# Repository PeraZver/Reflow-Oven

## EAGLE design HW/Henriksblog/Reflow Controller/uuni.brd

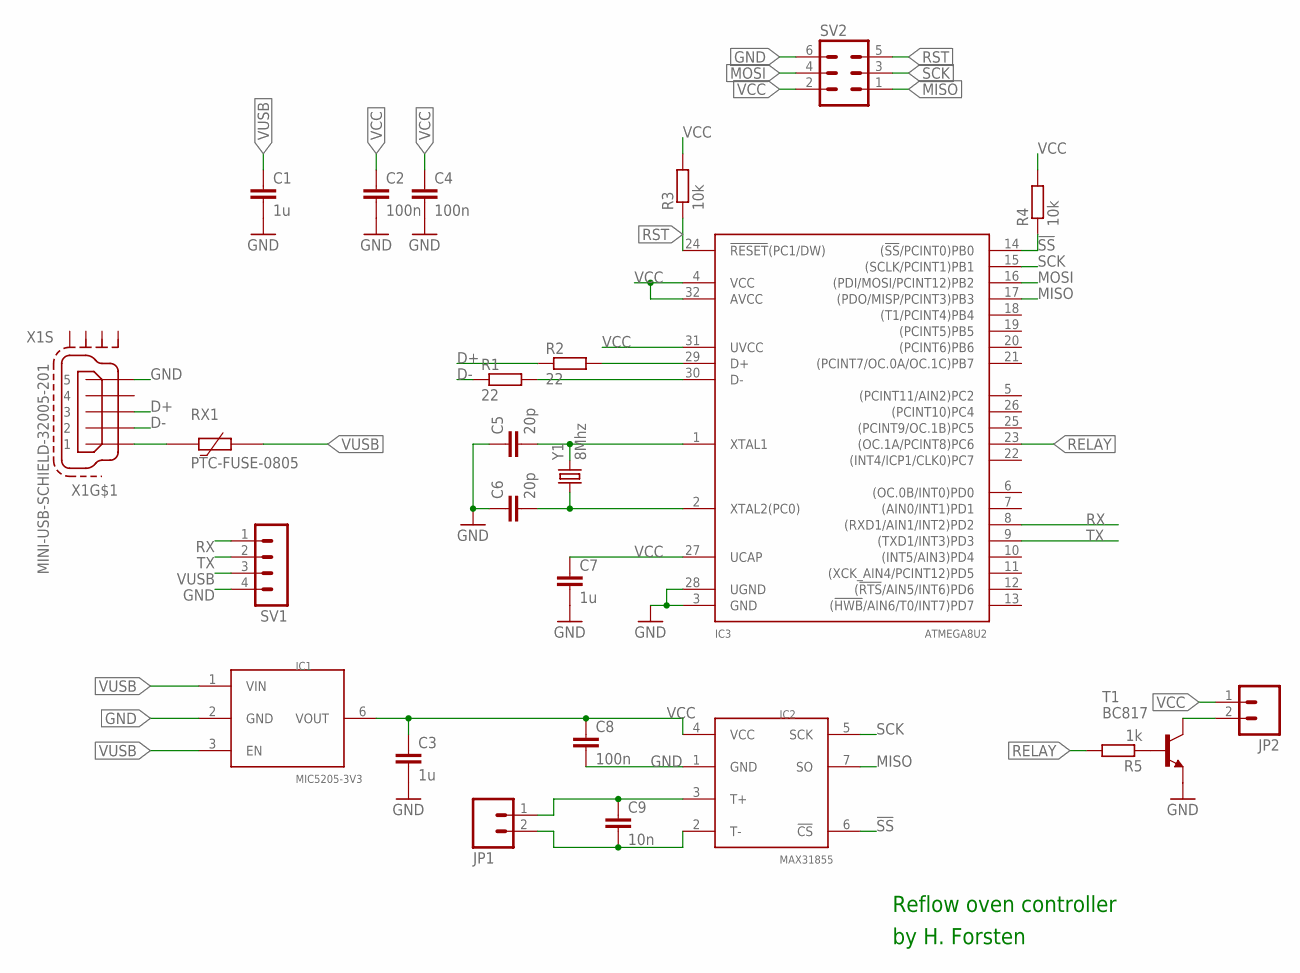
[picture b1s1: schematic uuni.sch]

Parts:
C1, C3, C7: 1u; C0603
C2, C4, C8: 100n; C0402
C5, C6: 20p; C0603
C9: 10n; C0603
IC1: MIC5205-3V3; SC-74
IC2: MAX31855; SO8
IC3: ATMEGA8U2; TQFP32-08
JP1: M025MM; SCREWTERMINAL-5MM-2
JP2: M02LOCK; 1X02_LOCK
R1, R2: 22; R0603
R3, R4: 10k; R0603
R5: 1k; R0603
RX1: PTC-FUSE-0805; R0805
SV1: MA04-1
SV2: MA03-2
T1: BC817; SOT23-BEC
X1: MINI-USB-SCHIELD-32005-201; 32005-201
Y1: 8Mhz; HC49UP

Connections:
!SS: IC2.6 (!CS), IC3.14 ((!SS!/PCINT0)PB0), R4.1
D+: R2.1, X1.3
D-: R1.1, X1.2
GND: C1.2, C2.2, C3.2, C4.2, C5.1, C6.1, C7.2, C8.2, IC1.2 (GND), IC2.1 (GND), IC3.3 (GND), IC3.28 (UGND), SV1.4, SV2.6, T1.E, X1.5
MISO: IC2.7 (SO), IC3.17 ((PDO/MISP/PCINT3)PB3), SV2.1
MOSI: IC3.16 ((PDI/MOSI/PCINT12)PB2), SV2.4
unnamed: C5.2, IC3.1 (XTAL1), Y1.2
unnamed: C6.2, IC3.2 (XTAL2(PC0)), Y1.1
unnamed: C9.1, IC2.3 (T+), JP1.1
unnamed: C9.2, IC2.2 (T-), JP1.2
unnamed: IC3.29 (D+), R2.2
unnamed: IC3.30 (D-), R1.2
unnamed: RX1.1, X1.1
unnamed: JP2.2, T1.C
unnamed: R5.1, T1.B
RELAY: IC3.23 ((OC.1A/PCINT8)PC6), R5.2
RST: IC3.24 (!RESET!(PC1/DW)), R3.1, SV2.5
RX: IC3.8 ((RXD1/AIN1/INT2)PD2), SV1.1
SCK: IC2.5 (SCK), IC3.15 ((SCLK/PCINT1)PB1), SV2.3
TX: IC3.9 ((TXD1/INT3)PD3), SV1.2
VCC: C2.1, C3.1, C4.1, C7.1, C8.1, IC1.6 (VOUT), IC2.4 (VCC), IC3.4 (VCC), IC3.27 (UCAP), IC3.31 (UVCC), IC3.32 (AVCC), JP2.1, R3.2, R4.2, SV2.2
VUSB: C1.1, IC1.1 (VIN), IC1.3 (EN), RX1.2, SV1.3

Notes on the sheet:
Reflow oven controller
by H. Forsten

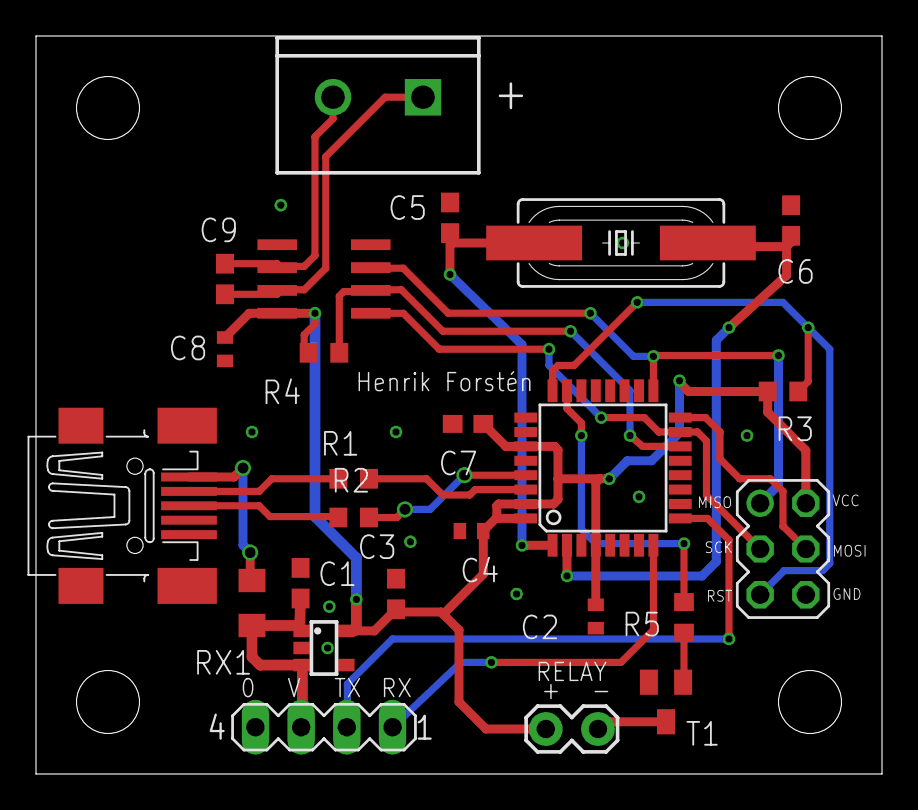
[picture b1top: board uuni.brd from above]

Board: 2 copper layers, 47.0 x 41.0 mm, 25 parts (0 on the bottom side), 22 nets.

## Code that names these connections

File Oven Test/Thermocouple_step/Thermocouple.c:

/* Pero 2015
*
*
* Step response 
* ATmega8u2
*
* The program measures the step response of the oven from MAX31855
* thermocouple amplifier via SPI. The oven is turned on by the PWM signal
* from A channel of the Timer1. 
*
* The microcontroller communicates with the PC via LUFA interface. 
*
* Code adapted from Henrik Forsten
*
* July 2015
*/



#include "Thermocouple.h"
/* SPI ports on first 4 pins of PORTB (PB0..3) */
#define SS 0
#define SCK 1
#define MOSI 2
#define MISO 3

static volatile bool usb_connected = 0;

static uint16_t room_temp = 0;

static FILE USBSerialStream;

USB_ClassInfo_CDC_Device_t VirtualSerial_CDC_Interface =
	{
		.Config =
			{
				.ControlInterfaceNumber   = 0,
				.DataINEndpoint           =
					{
						.Address          = CDC_TX_EPADDR,
						.Size             = CDC_TXRX_EPSIZE,
						.Banks            = 1,
					},
				.DataOUTEndpoint =
					{
						.Address          = CDC_RX_EPADDR,
						.Size             = CDC_TXRX_EPSIZE,
						.Banks            = 1,
					},
				.NotificationEndpoint =
					{
						.Address          = CDC_NOTIFICATION_EPADDR,
						.Size             = CDC_NOTIFICATION_EPSIZE,
						.Banks            = 1,
					},
			},
	};




uint16_t read_sensor(void) {
/* Bits:
 * 31 : sign,
 * 30 - 18 : thermocouple temperature,
 * 17 : reserved(0),
 * 16 : 1 if fault,
 * 15 - 4 : cold junction temperature,
 * 3 : reserved(0),
 * 2 : 1 if thermocouple is shorted to Vcc,
 * 1 : 1 if thermocouple is shorted to ground,
 * 0 : 1 if thermocouple is open circuit */

    /* Enable slave */
    uint8_t sensor[4];
    uint16_t temp;
    int8_t i;
    /* SS = 0 */
    PORTB = (0<<SS);

    /* Wait for the device */
    _NOP();
    _NOP();
    /* Transmit nothing */
    for(i=0;i<4;i++) {
        SPDR = 0x00;
        /* Wait for transmission to complete */
        while (!(SPSR & _BV(SPIF)));
        sensor[i] = SPDR;
    }

    /* Thermocouple temperature */
    if (sensor[0]&(1<<7)) {
        /* Negative temperature, clamp it to zero */
        temp = 0;
    } else {
        temp = (((uint16_t)sensor[0])<<6)+(sensor[1]>>2);
    }

    /* Room temperature */
    if (sensor[2]&(1<<7)) {
        /* Negative temperature, clamp it to zero */
        room_temp = 0;
    } else {
        room_temp = (((uint16_t)sensor[2])<<4)+(sensor[3]>>4);
        /* Sensor gives room temp as sixteenths of celsius,
         * divide it by four to get quarters of celsius. */
        room_temp = room_temp / 4;
    }

    if (sensor[1]&0x01) {
        /* Fault */
        fprintf(&USBSerialStream,"Fault:%u\n",sensor[3]&0b00000111);
    }

    /* Disable slave */
    PORTB = (1<<SS);
    return temp;
}

void setupHardware(void) {

    /* Disable wtachdog */
    MCUSR &= ~(1 << WDRF);
	wdt_disable();
    /* Disable prescaler */
	clock_prescale_set(clock_div_1);
	
	
	/******** Timer Setup **********/

    /* Set timer1 to count 1 second */
    TCNT1 = 0x0000;
    /* PWM output to channel A, pin PC6 */
    TCCR1A = 0b10000010;   // Output on Channel A (pin23, PC6), Fast PWM, COM1A1 = 10 - Clear OC1A on compare match, set at TOP
    /*  Set prescaler to divide by 256 for TMR1 */
    TCCR1B = 0b11011100;   // Fast PWM, CS1 = 100-prescale 256, together with TCCR1A, WGM is 1110 - Fast PWM, TOP is in ICR1, Update of OCR1A at TOP, 
    ICR1 = _ICR1;   // only Used for defining TOP Value: _ICR1 = 6250, presc=256 what means PWM frequnecy is 5Hz
    OCR1A = 625;       //  OFF value for the PWM, duty cycle is 625/6250 = 10%

    /* PC6 = Relay */
    DDRC   = 0b01000000;   // XTAL2 is on PC0, make it as input, Relay is on PC6, make it output
    PORTC  = 0x00;		   // Turn the relay down
    DDRD   = 0x00;         // Nothing, except UART which is unused.
	
	
	/******* SPI Setup **********/

    /* Enable SPI, Master, set clock rate fck/2 */
    SPCR = (1<<SPE) | (1<<MSTR);
    SPSR = (1<<SPI2X);
	/* Set !SS and SCK output, all others input */
    DDRB = (1<<SS)|(1<<SCK);
	PORTB |= (1<<SS);
	PORTB &= ~(1<<SCK);

 
 
	/******** USB Setup ***********/
	
    /* Initialize USB */
    USB_Init();
    CDC_Device_CreateStream(&VirtualSerial_CDC_Interface, &USBSerialStream);

    return;
}


int main(void) {


    bool tx_flag = 0;
    uint16_t temp = 0;
	
    setupHardware();
	GlobalInterruptEnable();

    temp = read_sensor();

    while(1)
    {
        if (usb_connected) {
            CDC_Device_USBTask(&VirtualSerial_CDC_Interface);
            USB_USBTask();
       }

        if (usb_connected && tx_flag) {
            tx_flag = 0;
            /* Send temp temperature */
			fprintf(&USBSerialStream, "temp:%u,room:%u,PWM:%u", (temp>>2), (room_temp>>2),OCR1A);
            fprintf(&USBSerialStream, "\n");
        }
		_delay_ms(250);
		/* Read the current temperature, updates temp and room_temp */
		temp = read_sensor();
		tx_flag = 1;
        
    }
}


/** Event handler for the library USB Connection event. */
void EVENT_USB_Device_Connect(void)
{
    usb_connected = 1;
}

/** Event handler for the library USB Disconnection event. */
void EVENT_USB_Device_Disconnect(void)
{
    usb_connected = 0;
}

/** Event handler for the library USB Configuration Changed event. */
void EVENT_USB_Device_ConfigurationChanged(void)
{
	CDC_Device_ConfigureEndpoints(&VirtualSerial_CDC_Interface);
}

/** Event handler for the library USB Control Request reception event. */
void EVENT_USB_Device_ControlRequest(void)
{
	CDC_Device_ProcessControlRequest(&VirtualSerial_CDC_Interface);
}

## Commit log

2016-04-14 Save all Reflow Oven Data, mine and Henriks all!!

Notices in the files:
parts and their libraries:
SparkFun-FreqCtrl: Licensing: CC v3.0 Share-Alike You are welcome to use this library for commercial purposes.
